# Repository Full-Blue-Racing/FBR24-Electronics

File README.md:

# FBR24-Electronics

This repo houses all the code the car needs to run, separated into steering 
wheel, telemetry, and CAN bus files.

# Git Gud

[Git Crash Course](https://rogerdudler.github.io/git-guide/)

[Gitlab SSH setup](https://docs.gitlab.com/ee/ssh/)

Git can be separated into remote and local repository (repo), how it works is 
that you can *clone* a repo to your local machine, *add* files you would like 
git to track, *commit* your changes to your local branch, *pull* changes by 
others from the remote repo, and *push* your own local changes. Locally git can 
be separated into three areas:

```Untracked files -> tracked files -> staging area```

Untracked files are usually not part of the project and will not be added to the
repo. Tracked files are project files, and files in here will have status shown 
(i.e. new file/changed/renamed...). The staging area is files that are ready to 
be *committed*, and tracked files needs to be added by ```git add```.

These are the only commands I would recommend using on the command line/IDE, 
for more complex commands (such as creating pull requests for merging branches) 
use the web interface. 

# Best Practices

### No spaces in file names or folder names please

**No direct pushing/committing on the master branch**

1. Use branches

Each of the following tasks are on a separate 
branch, please work on the branch relevant to your task. If multiple people are 
on the same branch please make sub-branches from the main task branch 

*e.g.* 
```
steering-wheel -> steering-wheel-warninglights
               -> steering-wheel-RPM-lights
```

We will merge them into the main steering-wheel branch when you make a merge 
request to the task branch.

2. Micro-commit

Commit every time you've implemented a feature - it allows easy rollback to 
previous version without too much code loss if things go wrong (and they *WILL* 
go wrong).

3. Handy commands

```git config --global user.name <display name>``` - sets your name on your commits to the repo

```git clone <path/to/directory>``` - clones a local copy of the repo to your
machine so you can make changes.

```git pull origin <name of branch>``` - pulls any changes others have 
published on the remote branch of the said name since your last update/ initial 
clone

```git add <file to be added>``` - adds file to the staging area to be included 
in the next commit.

```git commit -m "Commit message here"``` - commits file to the local branch 
with the commit message - please make the commit message meaningful so it is 
easier to backtrack (**Not** ```Add new file```) 

```git push origin <name of branch>``` - push your local commits to the remote 
repo on the named branch. Note that on the first push git may require you to 
set the upstream branch with ```git branch --set-upstream-to <name of head branch>```

```git remote update origin --prune``` - updates branches and removes merged branches 
on your local machine.

# Tasks

Each function to be made are described in respective folders' ```README```,
please edit the ```README``` with your name if you are currently working on the 
task, and remove it if not. If someone is already working on one and you want 
to join, contact them and see if you can help before writing your own code. 
Otherwise just write your name down and contact me (Will) for any 
questions/purchasing.

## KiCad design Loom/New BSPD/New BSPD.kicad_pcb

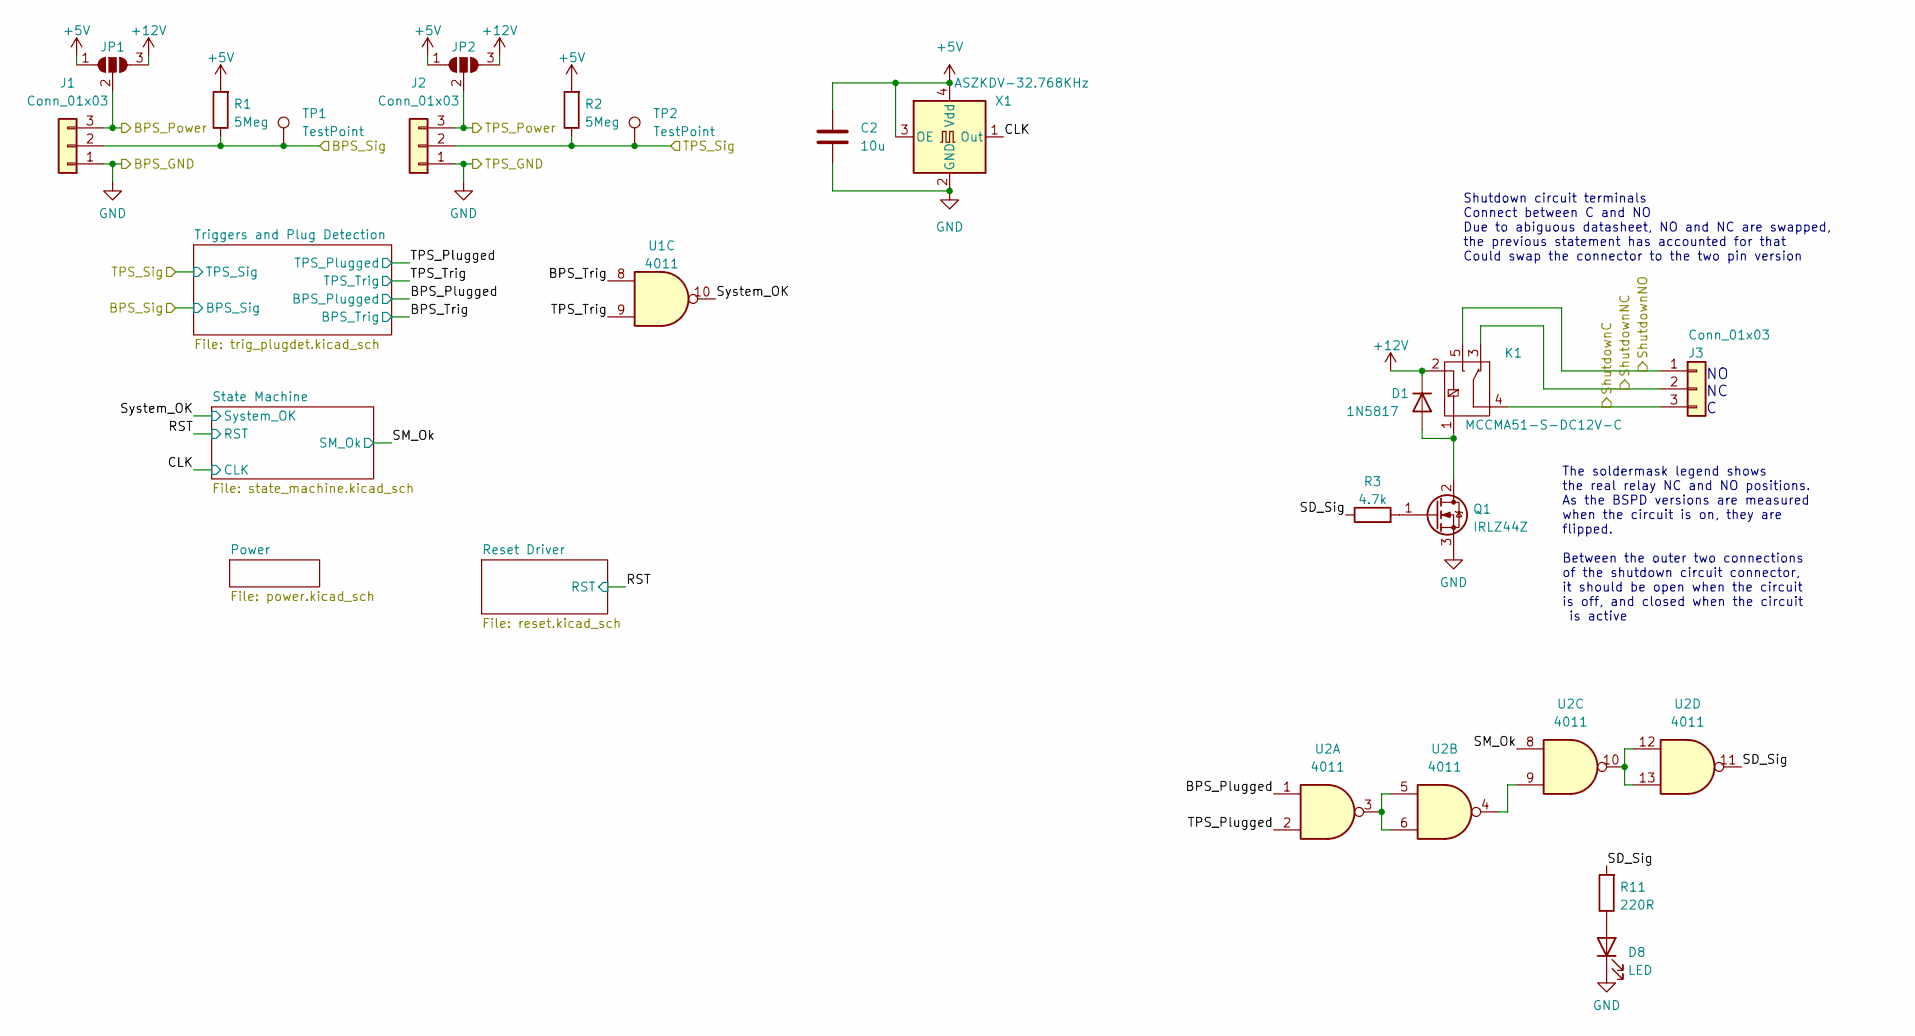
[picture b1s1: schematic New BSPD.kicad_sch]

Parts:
C2: 10u; C_0603_1608Metric_Pad1.08x0.95mm_HandSolder
D1: 1N5817; D_DO-41_SOD81_P10.16mm_Horizontal
D8: LED; LED_D5.0mm
J1, J2, J3: Conn_01x03; ATF13-3P-BM03
JP1, JP2: SolderJumper_3_Open; SolderJumper-3_P1.3mm_Open_RoundedPad1.0x1.5mm
K1: MCCMA51-S-DC12V-C
Q1: IRLZ44Z; TO-220-3_Horizontal_TabDown
R1, R2: 5Meg; R_Axial_DIN0207_L6.3mm_D2.5mm_P7.62mm_Horizontal
R3: 4.7k; R_Axial_DIN0207_L6.3mm_D2.5mm_P7.62mm_Horizontal
R11: 220R; R_Axial_DIN0207_L6.3mm_D2.5mm_P7.62mm_Horizontal
TP1, TP2: TestPoint; TestPoint_THTPad_D3.0mm_Drill1.5mm
U1, U2: 4011; DIP-14_W7.62mm_Socket
X1: ASZKDV-32.768KHz; Oscillator_SMD_Abracon_ASE-4Pin_3.2x2.5mm

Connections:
+5V: C2.1, JP1.1 (A), JP2.1 (A), R1.2, R2.2, X1.3 (OE), X1.4 (Vdd); also elsewhere on the board
+12V: D1.1 (K), JP1.3 (B), JP2.3 (B), K1.2; also elsewhere on the board
/BPS_Plugged: U2.1; also elsewhere on the board
/BPS_Power: J1.3, JP1.2 (C)
/BPS_Sig: J1.2, R1.1, TP1.1; also elsewhere on the board
/BPS_Trig: U1.8; also elsewhere on the board
/CLK: X1.1 (Out); also elsewhere on the board
/SD_Sig: R3.1, R11.2, U2.11
/SM_Ok: U2.8; also elsewhere on the board
/ShutdownC: J3.3, K1.4
/ShutdownNC: J3.2, K1.3
/ShutdownNO: J3.1, K1.5
/System_OK: U1.10; also elsewhere on the board
/TPS_Plugged: U2.2; also elsewhere on the board
/TPS_Power: J2.3, JP2.2 (C)
/TPS_Sig: J2.2, R2.1, TP2.1; also elsewhere on the board
/TPS_Trig: U1.9; also elsewhere on the board
GND: C2.2, D8.1 (K), J1.1, J2.1, Q1.3 (S), X1.2 (GND); also elsewhere on the board
unnamed: D1.2 (A), K1.1, Q1.2 (D)
unnamed: D8.2 (A), R11.1
unnamed: Q1.1 (G), R3.2
unnamed: U2.3, U2.5, U2.6
unnamed: U2.4, U2.9
unnamed: U2.10, U2.12, U2.13

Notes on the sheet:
NO NC C
The soldermask legend shows the real relay NC and NO positions. As the BSPD versions are measured when the circuit is on, they are flipped. Between the outer two connections of the shutdown circuit connector, it should be open when the circuit is off, and closed when the circuit is active
Shutdown circuit terminals Connect between C and NO Due to abiguous datasheet, NO and NC are swapped, the previous statement has accounted for that Could swap the connector to the two pin version

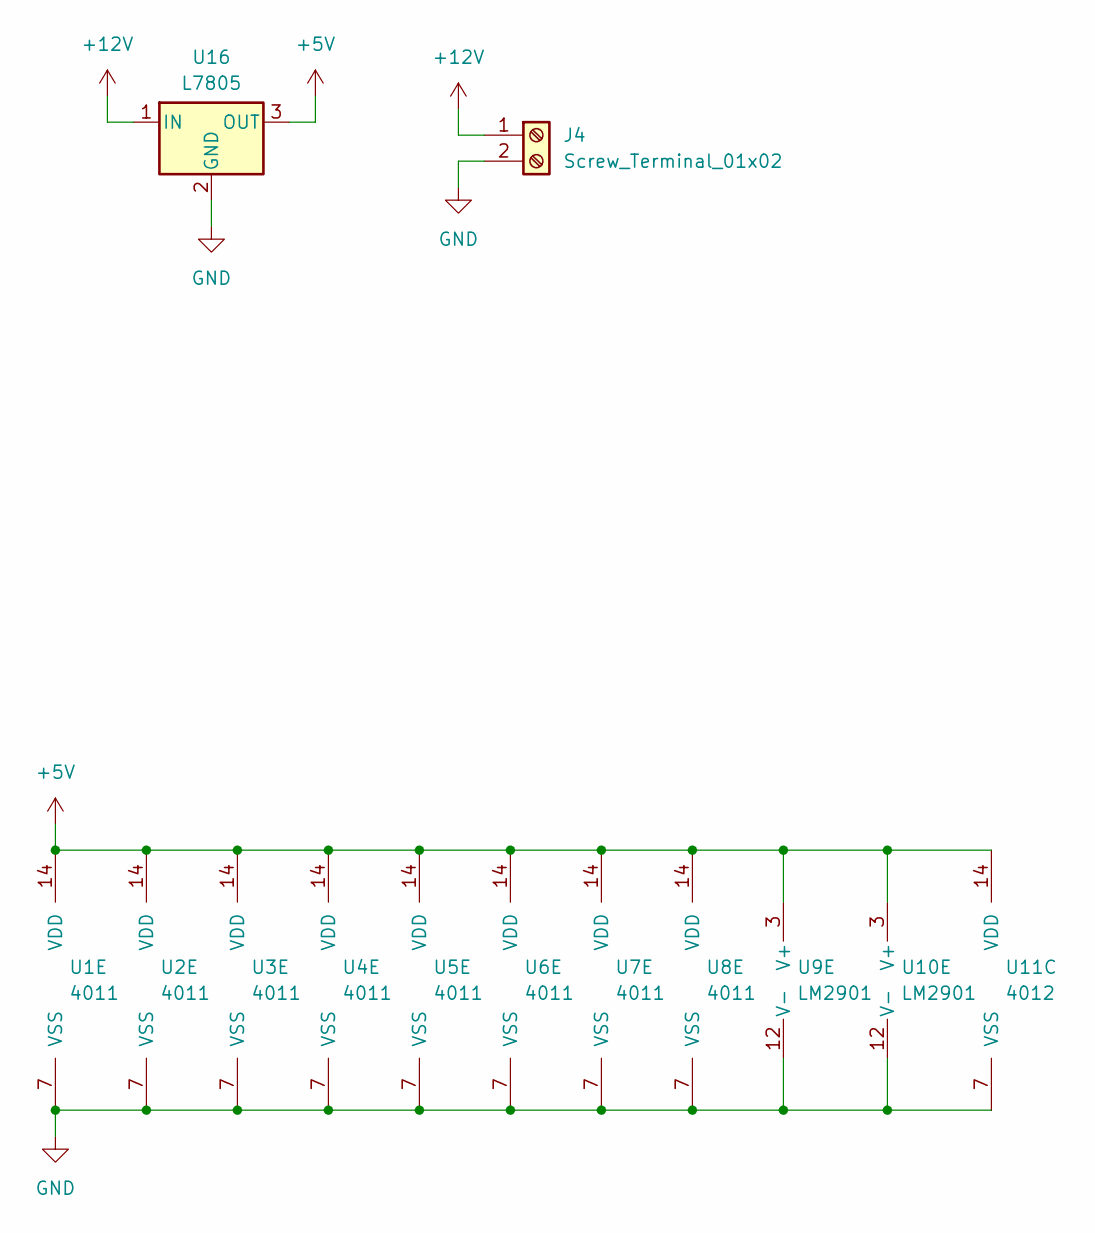
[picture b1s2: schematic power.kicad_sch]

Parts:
J4: Screw_Terminal_01x02; ATF13-2P-BM03
U1, U2, U3, U4, U5, U6, U7, U8: 4011; DIP-14_W7.62mm_Socket
U9, U10: LM2901; DIP-14_W7.62mm_Socket
U11: 4012; DIP-14_W7.62mm_Socket
U16: L7805; TO-220-3_Horizontal_TabDown

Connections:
+5V: U1.14 (VDD), U2.14 (VDD), U3.14 (VDD), U4.14 (VDD), U5.14 (VDD), U6.14 (VDD), U7.14 (VDD), U8.14 (VDD), U9.3 (V+), U10.3 (V+), U11.14 (VDD), U16.3 (OUT); also elsewhere on the board
+12V: J4.1, U16.1 (IN); also elsewhere on the board
GND: J4.2, U1.7 (VSS), U2.7 (VSS), U3.7 (VSS), U4.7 (VSS), U5.7 (VSS), U6.7 (VSS), U7.7 (VSS), U8.7 (VSS), U9.12 (V-), U10.12 (V-), U11.7 (VSS), U16.2 (GND); also elsewhere on the board

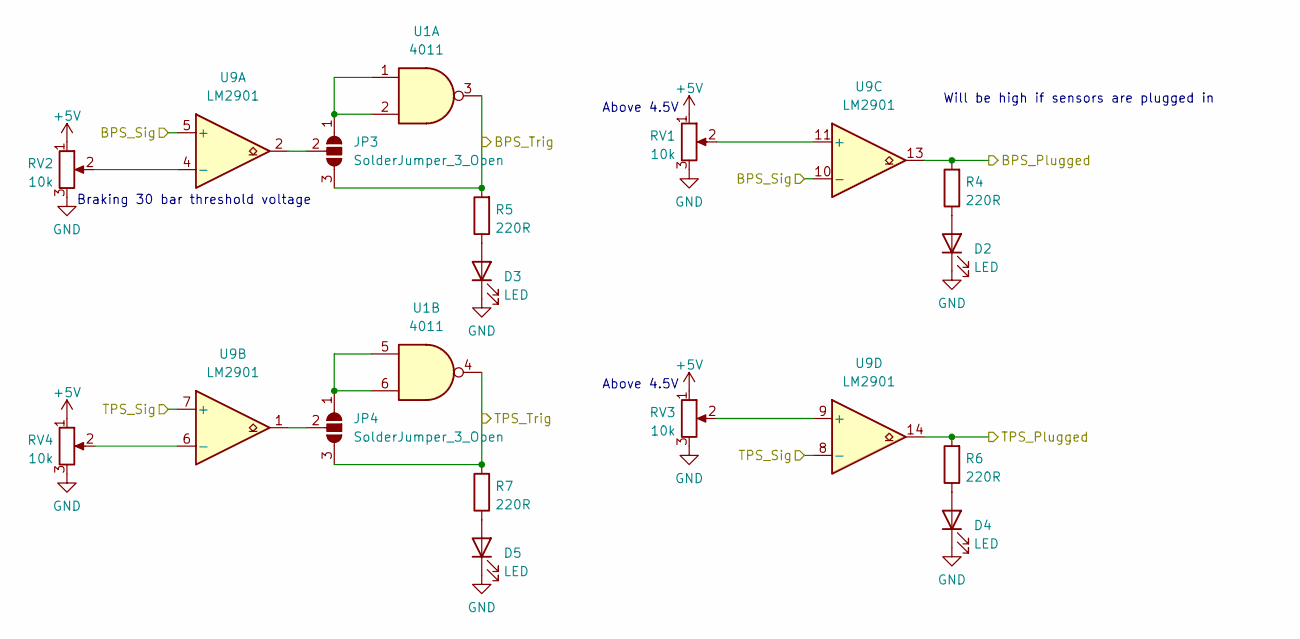
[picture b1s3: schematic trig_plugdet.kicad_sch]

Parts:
D2, D3, D4, D5: LED; LED_D5.0mm
JP3, JP4: SolderJumper_3_Open; SolderJumper-3_P1.3mm_Open_RoundedPad1.0x1.5mm
R4, R5, R6, R7: 220R; R_Axial_DIN0207_L6.3mm_D2.5mm_P7.62mm_Horizontal
RV1, RV2, RV3, RV4: 10k; Potentiometer_Bourns_3296Y_Vertical
U1: 4011; DIP-14_W7.62mm_Socket
U9: LM2901; DIP-14_W7.62mm_Socket

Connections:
+5V: RV1.1, RV2.1, RV3.1, RV4.1; also elsewhere on the board
/BPS_Plugged: R4.2, U9.13; also elsewhere on the board
/BPS_Sig: U9.5 (+), U9.10 (-); also elsewhere on the board
/BPS_Trig: JP3.3 (B), R5.2, U1.3; also elsewhere on the board
/TPS_Plugged: R6.2, U9.14; also elsewhere on the board
/TPS_Sig: U9.7 (+), U9.8 (-); also elsewhere on the board
/TPS_Trig: JP4.3 (B), R7.2, U1.4; also elsewhere on the board
GND: D2.1 (K), D3.1 (K), D4.1 (K), D5.1 (K), RV1.3, RV2.3, RV3.3, RV4.3; also elsewhere on the board
unnamed: D2.2 (A), R4.1
unnamed: D3.2 (A), R5.1
unnamed: D4.2 (A), R6.1
unnamed: D5.2 (A), R7.1
unnamed: JP3.1 (A), U1.1, U1.2
unnamed: JP3.2 (C), U9.2
unnamed: JP4.1 (A), U1.5, U1.6
unnamed: JP4.2 (C), U9.1
unnamed: RV2.2, U9.4 (-)
unnamed: RV4.2, U9.6 (-)
unnamed: RV1.2, U9.11 (+)
unnamed: RV3.2, U9.9 (+)

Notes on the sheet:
Will be high if sensors are plugged in
Above 4.5V
Braking 30 bar threshold voltage

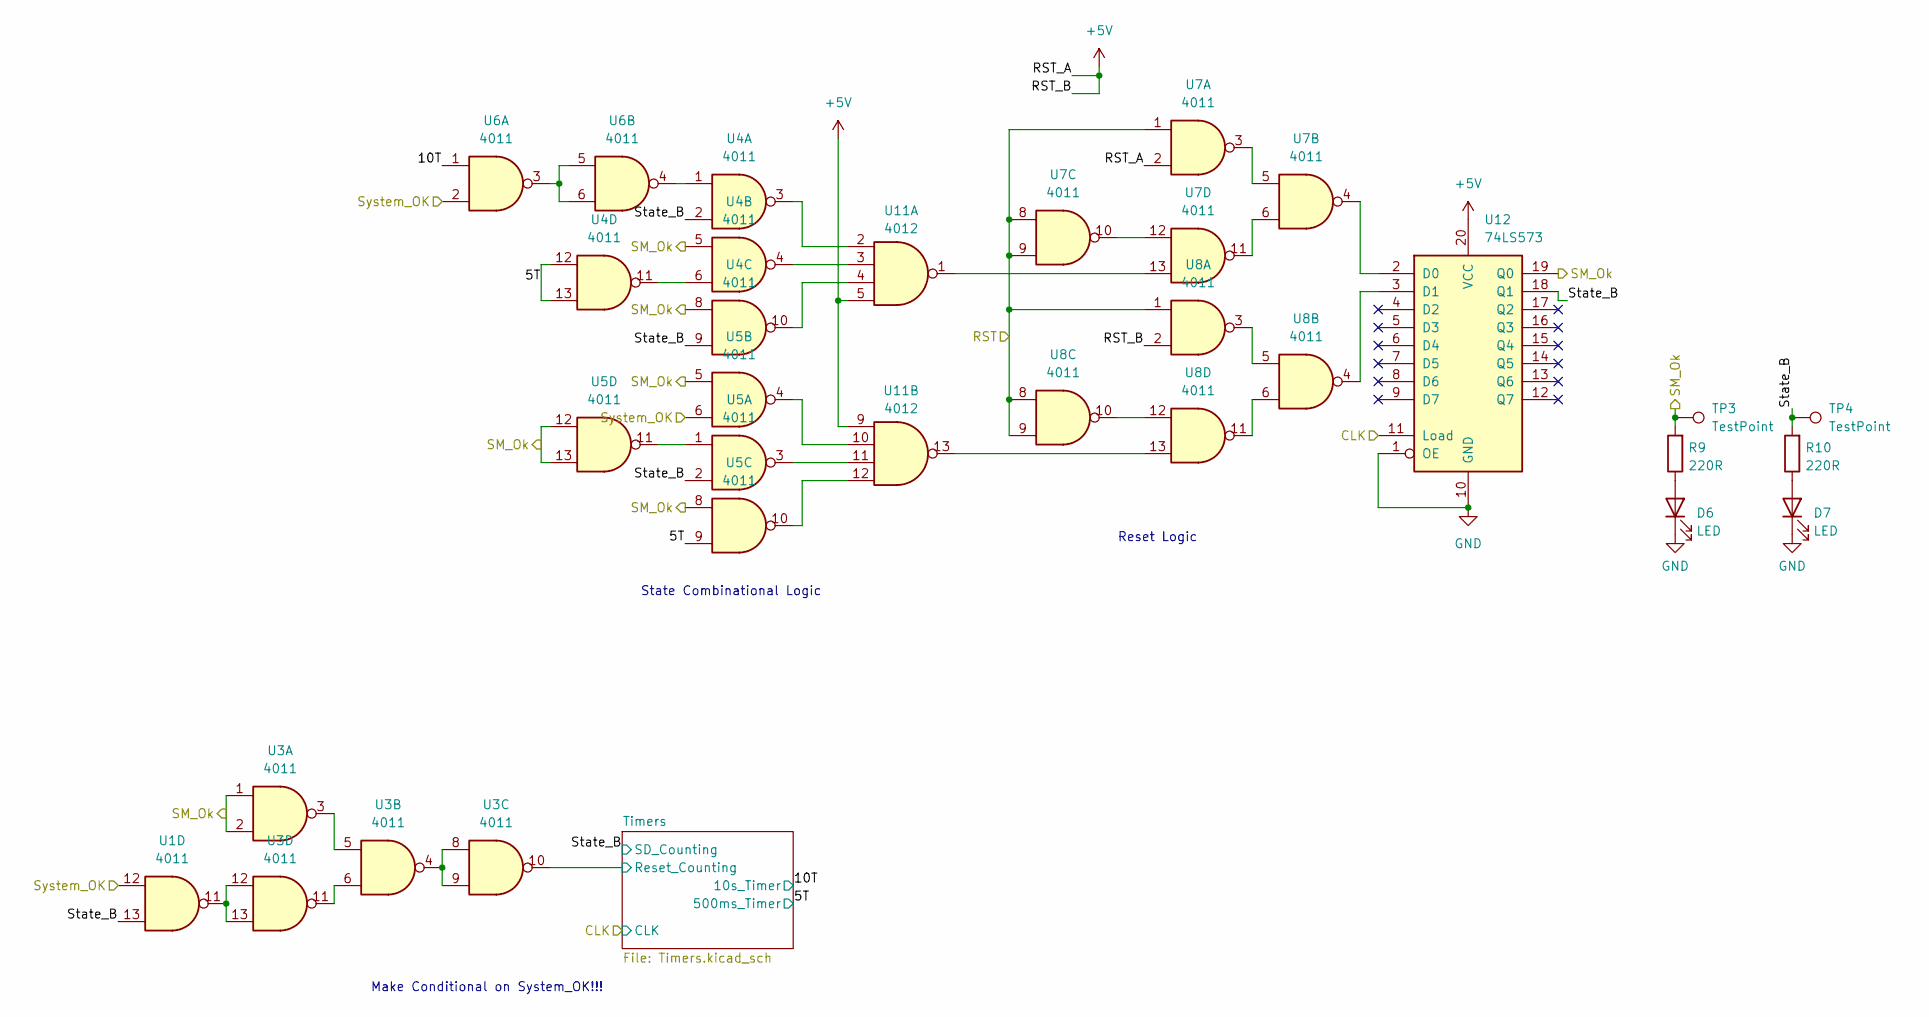
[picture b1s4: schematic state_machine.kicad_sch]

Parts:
D6, D7: LED; LED_D5.0mm
R9, R10: 220R; R_Axial_DIN0207_L6.3mm_D2.5mm_P7.62mm_Horizontal
TP3, TP4: TestPoint; TestPoint_THTPad_D3.0mm_Drill1.5mm
U1, U3, U4, U5, U6, U7, U8: 4011; DIP-14_W7.62mm_Socket
U11: 4012; DIP-14_W7.62mm_Socket
U12: 74LS573; DIP-20_W7.62mm_Socket

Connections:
+5V: U7.2, U8.2, U11.5, U11.9, U12.20 (VCC); also elsewhere on the board
/CLK: U12.11 (Load); also elsewhere on the board
/RST: U7.1, U7.8, U7.9, U8.1, U8.8, U8.9; also elsewhere on the board
/SM_Ok: R9.2, TP3.1, U3.1, U3.2, U4.5, U4.8, U5.5, U5.8, U5.12, U5.13, U12.19 (Q0); also elsewhere on the board
/State Machine/5T: U4.12, U4.13, U5.9; also elsewhere on the board
/State Machine/10T: U6.1; also elsewhere on the board
/State Machine/State_B: R10.2, TP4.1, U1.13, U4.2, U4.9, U5.2, U12.18 (Q1); also elsewhere on the board
/State Machine/Timers/Reset_Counting: U3.10; also elsewhere on the board
/System_OK: U1.12, U5.6, U6.2; also elsewhere on the board
GND: D6.1 (K), D7.1 (K), U12.1 (OE), U12.10 (GND); also elsewhere on the board
unnamed: D6.2 (A), R9.1
unnamed: D7.2 (A), R10.1
unnamed: U1.11, U3.12, U3.13
unnamed: U3.3, U3.5
unnamed: U3.4, U3.8, U3.9
unnamed: U3.6, U3.11
unnamed: U4.1, U6.4
unnamed: U4.6, U4.11
unnamed: U5.1, U5.11
unnamed: U6.3, U6.5, U6.6
unnamed: U7.3, U7.5
unnamed: U7.10, U7.12
unnamed: U7.6, U7.11
unnamed: U8.3, U8.5
unnamed: U8.10, U8.12
unnamed: U8.6, U8.11
unnamed: U7.13, U11.1
unnamed: U4.3, U11.2
unnamed: U4.4, U11.3
unnamed: U4.10, U11.4
unnamed: U5.4, U11.10
unnamed: U5.3, U11.11
unnamed: U5.10, U11.12
unnamed: U8.13, U11.13
unnamed: U7.4, U12.2 (D0)
unnamed: U8.4, U12.3 (D1)

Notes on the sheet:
Make Conditional on System_OK!!!
State Combinational Logic
Reset Logic

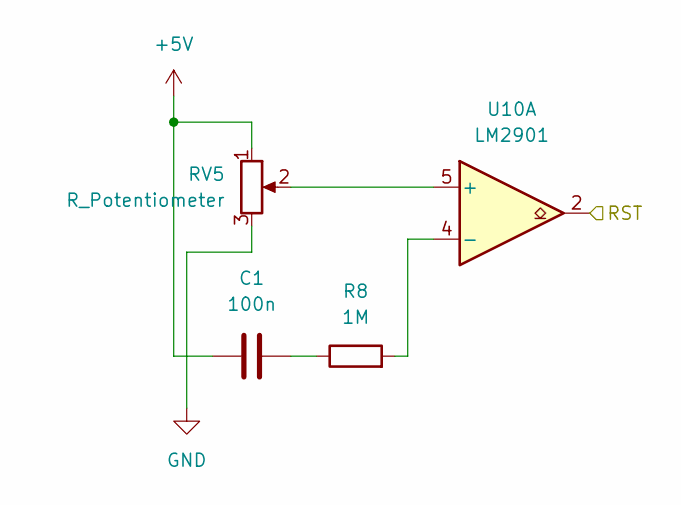
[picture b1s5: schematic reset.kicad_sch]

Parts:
C1: 100n; C_Disc_D5.0mm_W2.5mm_P5.00mm
R8: 1M; R_Axial_DIN0207_L6.3mm_D2.5mm_P7.62mm_Horizontal
RV5: R_Potentiometer; Potentiometer_Bourns_3296Y_Vertical
U10: LM2901; DIP-14_W7.62mm_Socket

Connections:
+5V: C1.1, RV5.1; also elsewhere on the board
/RST: U10.2; also elsewhere on the board
GND: RV5.3; also elsewhere on the board
unnamed: C1.2, R8.1
unnamed: RV5.2, U10.5 (+)
unnamed: R8.2, U10.4 (-)

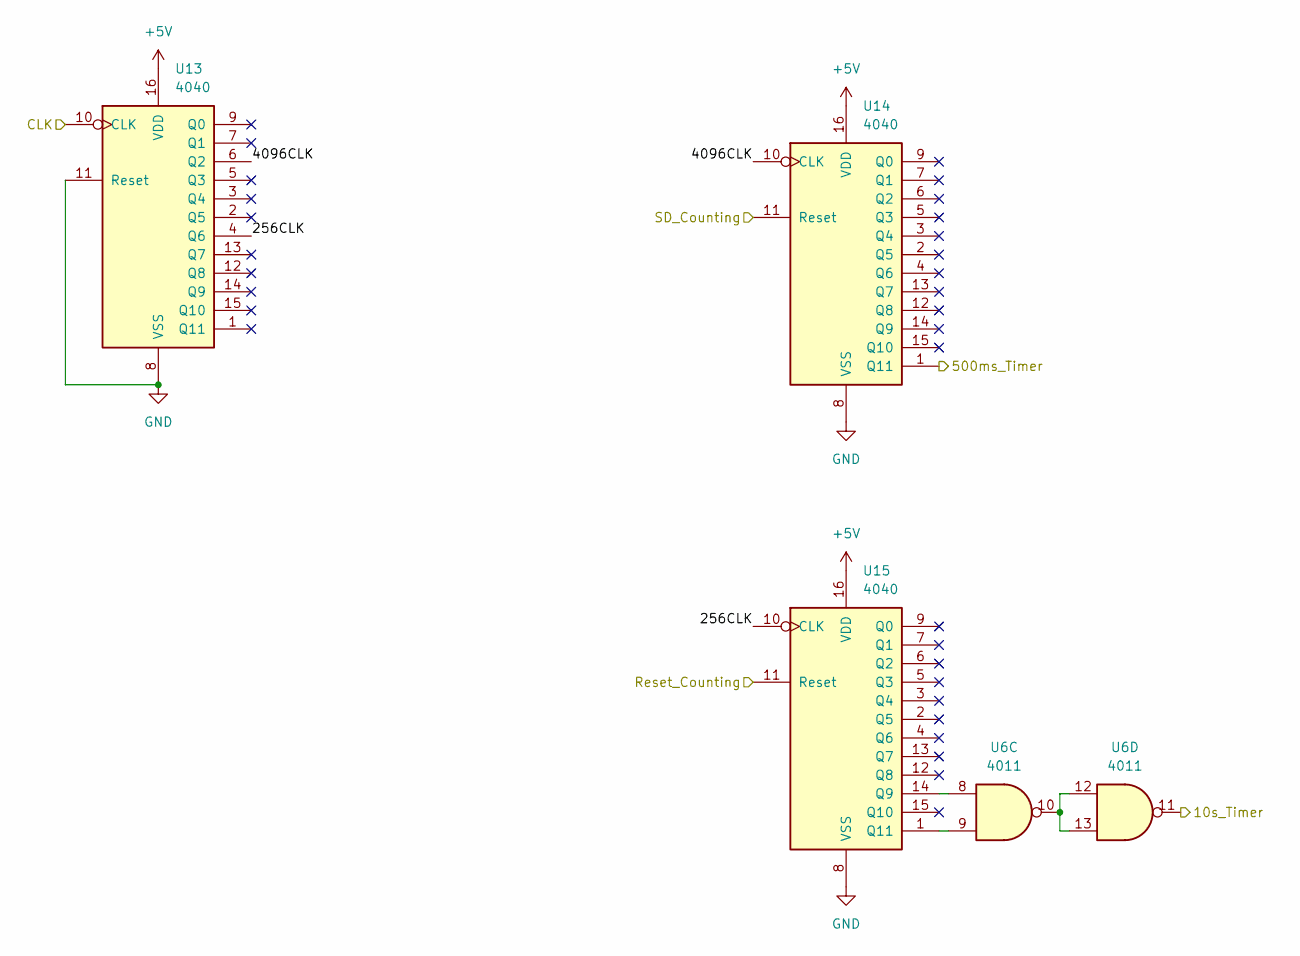
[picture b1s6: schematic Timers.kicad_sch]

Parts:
U6: 4011; DIP-14_W7.62mm_Socket
U13, U14, U15: 4040; DIP-16_W7.62mm_Socket

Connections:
+5V: U13.16 (VDD), U14.16 (VDD), U15.16 (VDD); also elsewhere on the board
/CLK: U13.10 (CLK); also elsewhere on the board
/State Machine/5T: U14.1 (Q11); also elsewhere on the board
/State Machine/10T: U6.11; also elsewhere on the board
/State Machine/State_B: U14.11 (Reset); also elsewhere on the board
/State Machine/Timers/256CLK: U13.4 (Q6), U15.10 (CLK)
/State Machine/Timers/4096CLK: U13.6 (Q2), U14.10 (CLK)
/State Machine/Timers/Reset_Counting: U15.11 (Reset); also elsewhere on the board
GND: U13.8 (VSS), U13.11 (Reset), U14.8 (VSS), U15.8 (VSS); also elsewhere on the board
unnamed: U6.10, U6.12, U6.13
unnamed: U6.8, U15.14 (Q9)
unnamed: U6.9, U15.1 (Q11)

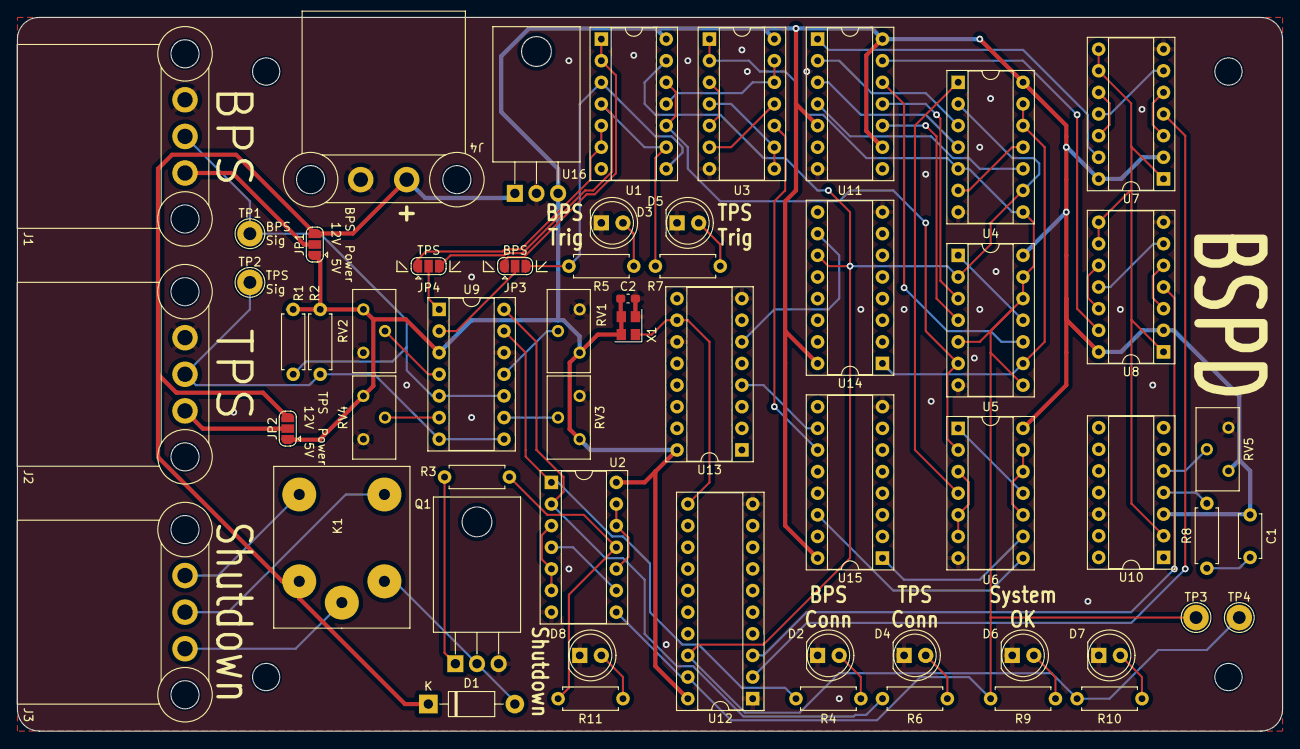
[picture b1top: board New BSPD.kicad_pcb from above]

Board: 2 copper layers, 148.6 x 83.8 mm, 61 parts (0 on the bottom side), 75 nets.

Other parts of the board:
MNT1, MNT2, MNT3, MNT4: MountingHole_3.2mm_M3

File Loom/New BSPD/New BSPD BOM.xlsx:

Component Count: | 46
Collated Components:
Item | Qty | Reference(s) | Value | LibPart | Footprint | Datasheet | DNP | Sim.Device | Sim.Pins
1 | 1 | C1 | C | Device:C |  | ~
2 | 1 | D1 | 1N5817 | Diode:1N4001 | Diode_THT:D_DO-41_SOD81_P10.16mm_Horizontal | http://www.vishay.com/docs/88503/1n4001.pdf |  | D | 1=K 2=A
3 | 4 | D2, D3, D4, D5 | LED | Device:LED | LED_THT:LED_D5.0mm | ~
4 | 2 | J1, J2 | 282087-1 | Connector:Conn_01x03_Female | Additional Footprints:3 pin flying lead | https://www.te.com/usa-en/product-282087-1.html
5 | 1 | J3 | 282105-1 | Connector:Conn_01x03_Female | Additional Footprints:3 pin flying lead | https://www.te.com/usa-en/product-282105-1.datasheet.pdf
6 | 1 | J4 | Screw_Terminal_01x02 | Connector:Screw_Terminal_01x02 |  | ~
7 | 4 | JP1, JP2, JP3, JP4 | SolderJumper_3_Open | Jumper:SolderJumper_3_Open | Jumper:SolderJumper-3_P1.3mm_Open_RoundedPad1.0x1.5mm | ~
8 | 1 | K1 | MCCMA51-S-DC12V-C | Additional_Components:Relay | Additional Footprints:MCCMA51-S-DC12V-C | https://www.farnell.com/datasheets/3169904.pdf
9 | 1 | Q1 | IRLZ44Z | Transistor_FET:IRLZ44N | Package_TO_SOT_THT:TO-220-3_Vertical | http://www.irf.com/product-info/datasheets/data/irlz44n.pdf
10 | 2 | R1, R2 | 5Meg | Device:R | Resistor_THT:R_Axial_DIN0207_L6.3mm_D2.5mm_P7.62mm_Horizontal | ~
11 | 1 | R3 | 4.7k | Device:R | Resistor_THT:R_Axial_DIN0207_L6.3mm_D2.5mm_P7.62mm_Horizontal | ~
12 | 4 | R4, R5, R6, R7 | 220R | Device:R | Resistor_THT:R_Axial_DIN0207_L6.3mm_D2.5mm_P7.62mm_Horizontal | ~
13 | 1 | R8 | R | Device:R |  | ~
14 | 4 | RV1, RV2, RV3, RV4 | 10k | Device:R_Potentiometer | Potentiometer_THT:Potentiometer_Bourns_3296Y_Vertical | ~
15 | 1 | RV5 | R_Potentiometer | Device:R_Potentiometer |  | ~
16 | 8 | U1, U2, U3, U4, U5, U6, U7, U8 | 4011 | 4xxx:4011 | Package_DIP:DIP-14_W7.62mm_Socket | http://www.intersil.com/content/dam/Intersil/documents/cd40/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
17 | 2 | U9, U10 | LM2901 | Comparator:LM2901 |  | https://www.st.com/resource/en/datasheet/lm2901.pdf
18 | 1 | U11 | 4012 | 4xxx:4012 | Package_DIP:DIP-14_W7.62mm_Socket | http://www.intersil.com/content/dam/Intersil/documents/cd40/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
19 | 1 | U12 | 74LS573 | 74xx:74LS573 |  | 74xx/74hc573.pdf
20 | 3 | U13, U14, U15 | 4040 | 4xxx:4040 |  | http://www.intersil.com/content/dam/Intersil/documents/cd40/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
21 | 1 | U16 | L7805 | Regulator_Linear:L7805 |  | http://www.st.com/content/ccc/resource/technical/document/da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
22 | 1 | X1 | ASZKDV-32.768KHz | BSPD Symbols:ASZKDV-xxxMHz | Oscillator:Oscillator_SMD_Abracon_ASE-4Pin_3.2x2.5mm | http://www.abracon.com/Oscillators/ASV.pdf

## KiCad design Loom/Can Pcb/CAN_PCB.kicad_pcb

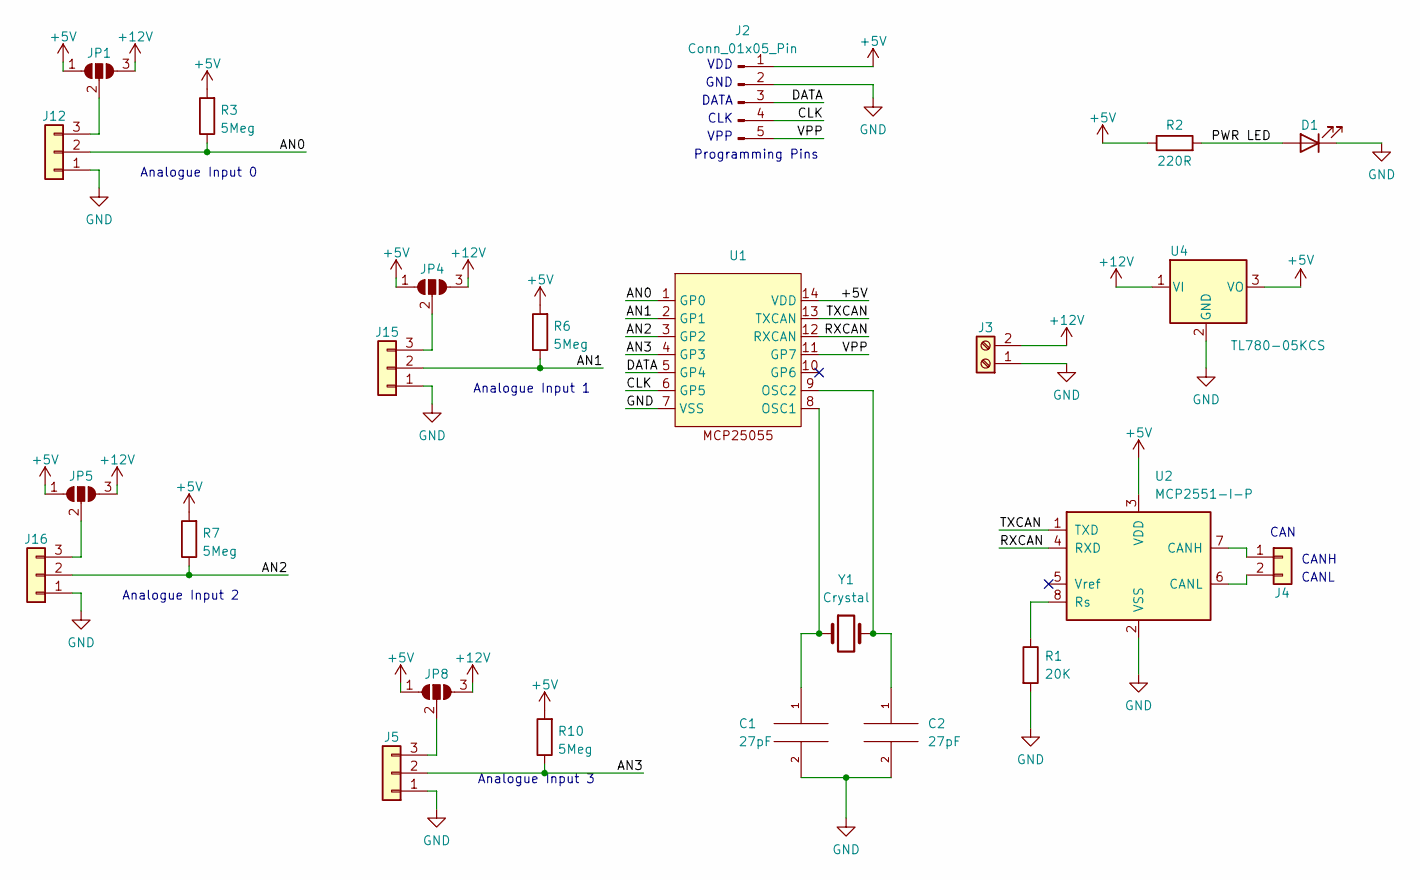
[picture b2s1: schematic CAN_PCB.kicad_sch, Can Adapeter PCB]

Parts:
C1, C2: 27pF; C_Disc_D4.7mm_W2.5mm_P5.00mm
D1: PWR LED; LED_D3.0mm
J2: Conn_01x05_Pin; PinHeader_1x05_P2.54mm_Vertical
J3: Screw_Terminal_01x02; TerminalBlock_bornier-2_P5.08mm
J4: Conn_01x02; ATF13-2P-BM03
J5, J12, J15, J16: Conn_01x03; ATF13-3P-BM03
JP1, JP4, JP5, JP8: SolderJumper_3_Open; SolderJumper-3_P1.3mm_Open_Pad1.0x1.5mm
R1: 20K; R_Axial_DIN0207_L6.3mm_D2.5mm_P7.62mm_Horizontal
R2: 220R; R_Axial_DIN0207_L6.3mm_D2.5mm_P7.62mm_Horizontal
R3, R6, R7, R10: 5Meg; R_Axial_DIN0207_L6.3mm_D2.5mm_P7.62mm_Horizontal
U1: DIP-14_W7.62mm_Socket
U2: MCP2551-I-P; DIP-8_W7.62mm_Socket
U4: TL780-05KCS; TO-220-3_Horizontal_TabDown
Y1: Crystal; 9B-16.000MAAJ-B

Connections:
+5V: J2.1, JP1.1 (A), JP4.1 (A), JP5.1 (A), JP8.1 (A), R2.1, R3.2, R6.2, R7.2, R10.2, U1.14 (VDD), U2.3 (VDD), U4.3 (VO)
+12V: J3.2, JP1.3 (B), JP4.3 (B), JP5.3 (B), JP8.3 (B), U4.1 (VI); also elsewhere on the board
/AN0: J12.2, R3.1, U1.1 (GP0)
/AN1: J15.2, R6.1, U1.2 (GP1)
/AN2: J16.2, R7.1, U1.3 (GP2)
/AN3: J5.2, R10.1, U1.4 (GP3)
/CLK: J2.4, U1.6 (GP5)
/DATA: J2.3, U1.5 (GP4)
/PWR LED: D1.2 (A), R2.2
/RXCAN: U1.12 (RXCAN), U2.4 (RXD)
/TXCAN: U1.13 (TXCAN), U2.1 (TXD)
/VPP: J2.5, U1.11 (GP7)
GND: C1.2, C2.2, D1.1 (K), J2.2, J3.1, J5.1, J12.1, J15.1, J16.1, R1.2, U1.7 (VSS), U2.2 (VSS), U4.2 (GND); also elsewhere on the board
unnamed: J4.1, U2.7 (CANH)
unnamed: J4.2, U2.6 (CANL)
unnamed: J5.3, JP8.2 (C)
unnamed: J12.3, JP1.2 (C)
unnamed: J15.3, JP4.2 (C)
unnamed: J16.3, JP5.2 (C)
unnamed: C1.1, U1.8 (OSC1), Y1.1
unnamed: C2.1, U1.9 (OSC2), Y1.2
unnamed: R1.1, U2.8 (Rs)

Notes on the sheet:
CAN
DATA
Analogue Input 2
VDD
Programming Pins
CANL
Analogue Input 3
Analogue Input 0
VPP
GND
CANH
CLK
Analogue Input 1

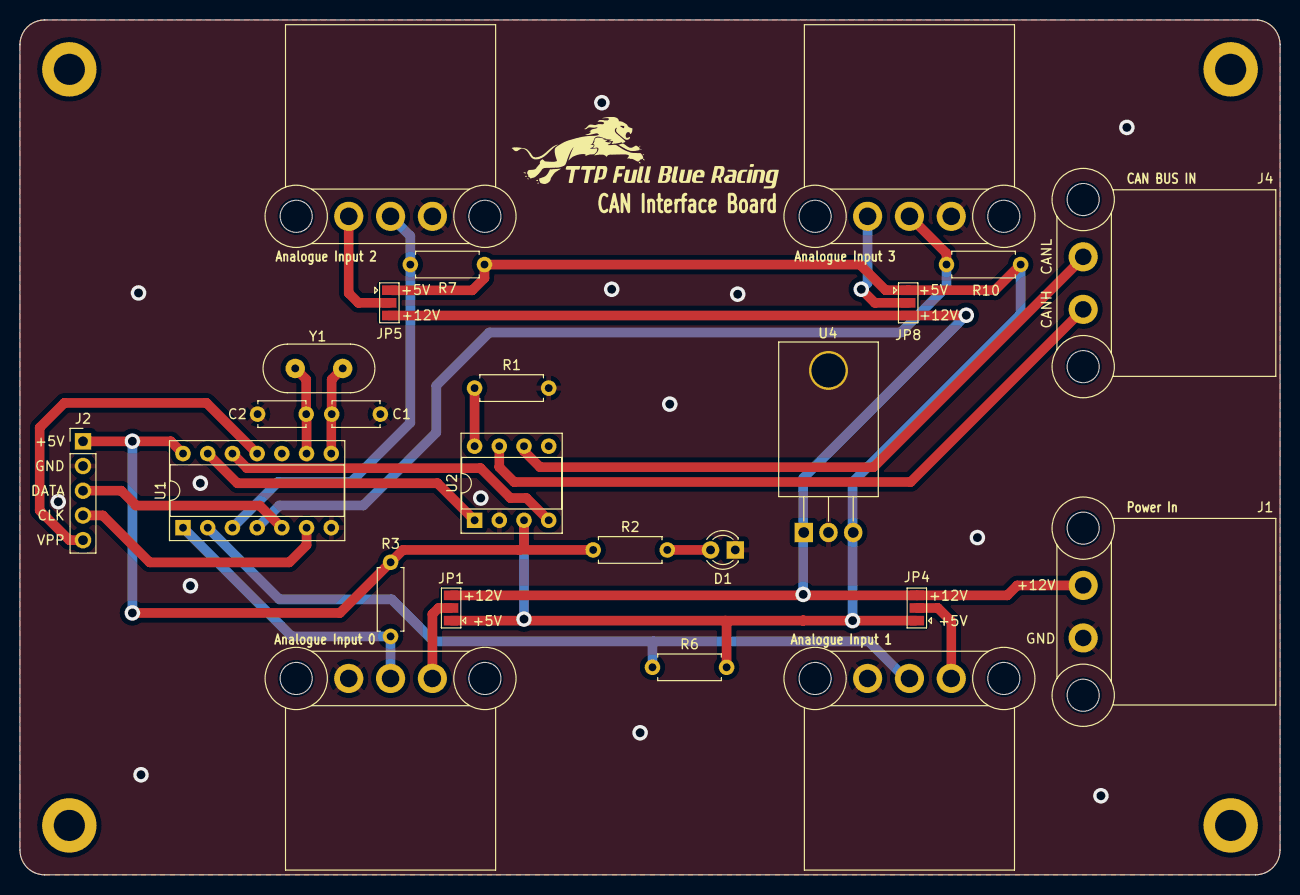
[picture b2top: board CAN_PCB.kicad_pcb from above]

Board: 2 copper layers, 129.5 x 87.9 mm, 24 parts (0 on the bottom side), 22 nets.

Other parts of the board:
J1: Conn_01x02; ATF13-2P-BM03

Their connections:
+12V: J1.2; also elsewhere on the board
GND: J1.1; also elsewhere on the board

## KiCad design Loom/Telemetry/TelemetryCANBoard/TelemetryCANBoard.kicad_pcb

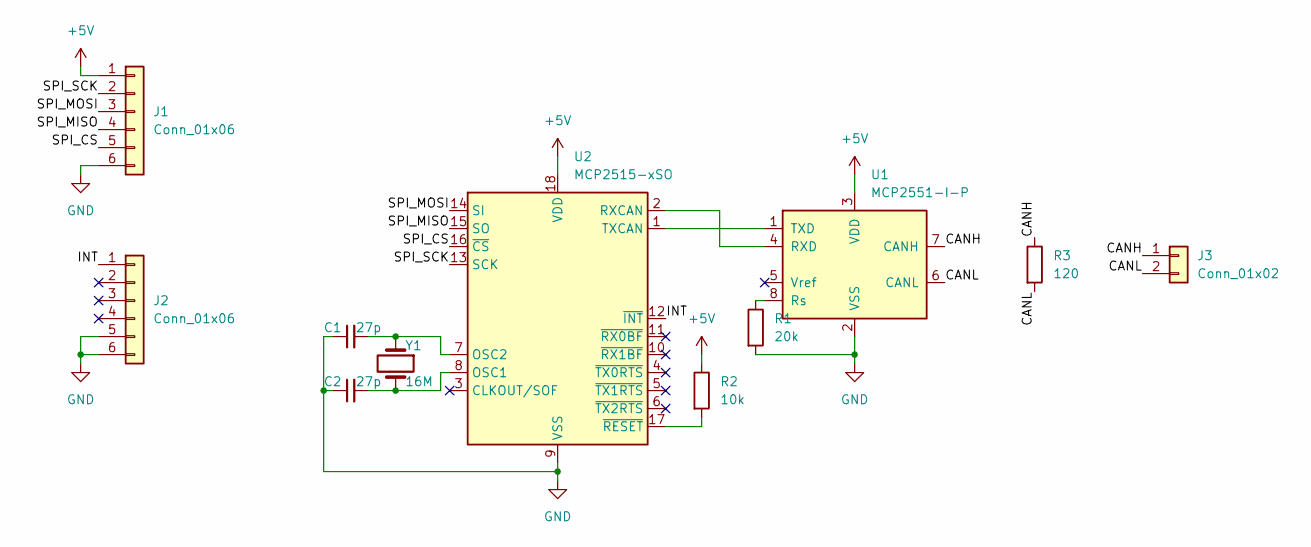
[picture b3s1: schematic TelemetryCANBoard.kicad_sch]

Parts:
C1, C2: 27p; C_Disc_D5.1mm_W3.2mm_P5.00mm
J1, J2: Conn_01x06; JST_XA_B06B-XASK-1_1x06_P2.50mm_Vertical
J3: Conn_01x02; ATF13-2P-BM03
R1: 20k; R_Axial_DIN0207_L6.3mm_D2.5mm_P7.62mm_Horizontal
R2: 10k; R_Axial_DIN0207_L6.3mm_D2.5mm_P7.62mm_Horizontal
R3: 120; R_Axial_DIN0207_L6.3mm_D2.5mm_P7.62mm_Horizontal
U1: MCP2551-I-P; DIP-8_W7.62mm
U2: MCP2515-xSO; DIP-18_W7.62mm
Y1: 16M; Crystal_HC49-U_Vertical

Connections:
+5V: J1.1, R2.1, U1.3 (VDD), U2.18 (VDD)
/CANH: J3.1, R3.1, U1.7 (CANH)
/CANL: J3.2, R3.2, U1.6 (CANL)
/INT: J2.1, U2.12 (~INT)
/SPI_CS: J1.5, U2.16 (~CS)
/SPI_MISO: J1.4, U2.15 (SO)
/SPI_MOSI: J1.3, U2.14 (SI)
/SPI_SCK: J1.2, U2.13 (SCK)
GND: C1.1, C2.1, J1.6, J2.5, J2.6, R1.2, U1.2 (VSS), U2.9 (VSS)
unnamed: U1.4 (RXD), U2.2 (RXCAN)
unnamed: R1.1, U1.8 (Rs)
unnamed: U1.1 (TXD), U2.1 (TXCAN)
unnamed: C2.2, U2.8 (OSC1), Y1.2
unnamed: C1.2, U2.7 (OSC2), Y1.1
unnamed: R2.2, U2.17 (~RESET)

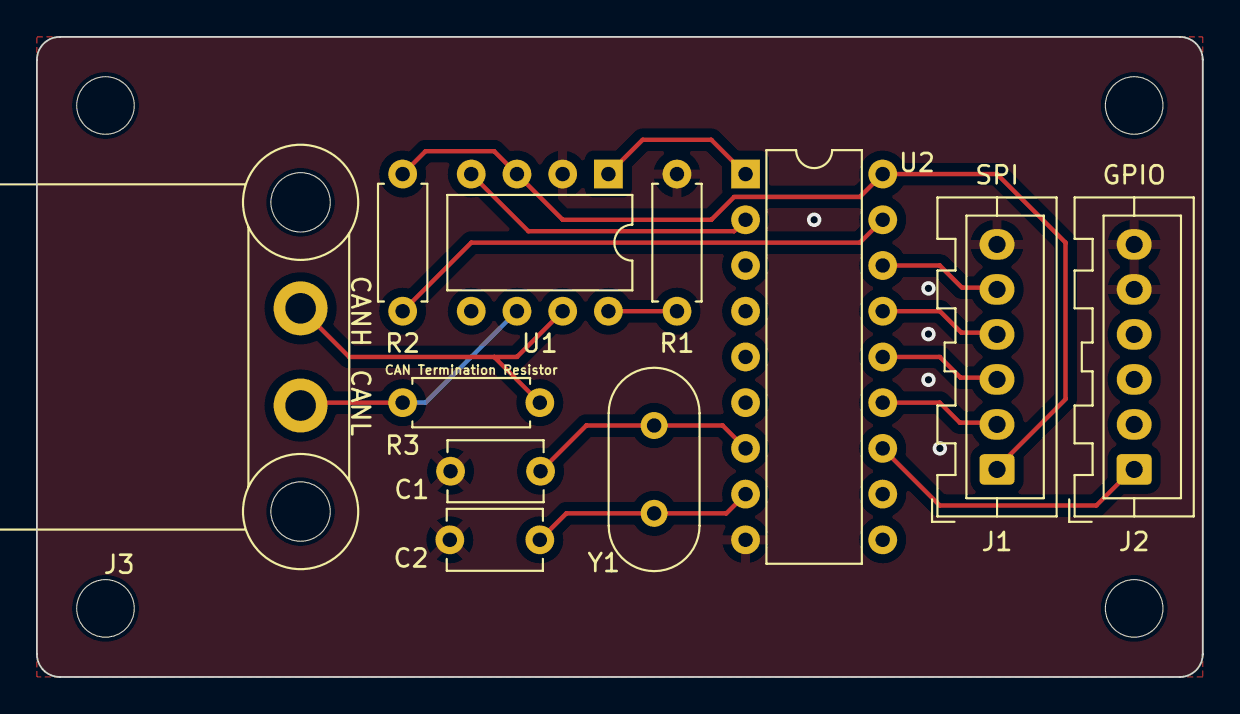
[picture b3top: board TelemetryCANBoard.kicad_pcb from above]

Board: 2 copper layers, 64.8 x 35.6 mm, 15 parts (0 on the bottom side), 15 nets.

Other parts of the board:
MNT1, MNT3, MNT4: MountingHole_3.2mm_M3
MNT2: MountingHole_3.2mm_M; MountingHole_3.2mm_M3
